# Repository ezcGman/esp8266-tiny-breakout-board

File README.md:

# ESP8266 Tiny Breakout Board
A very small (29,9x26,9mm) ESP8266 breakout board with 5V support, proper screw terminal for power wires and required resistors and caps for the ADC input!

## Credits
As for all my PCBs: Huge thanks to Quindor from QuinLED.info and also the folks from #pcb-design-talk on his Discord server! Would not have been able to do anything without these people!!

## KiCad dependencies
It might happen that KiCad is missing my custom footprints. You can find and download them here and then add them to KiCad: https://github.com/ezcGman/andys-footprints

## Key features
- It's small! A little smaller even than these cheap / billo breakout boards you bought so far on AliExpress or eBay!
- It's a real PCB and not that paper thing I just ranted about in the line above!
- 5-18V support! However, I recommend powering it with 12V max; the heat that LDO will produce might be a bit much.
- The ESP sits on pin headers instead of being soldered onto it. This enables you to remove / exchange it, e.g. if your code on that ESP doesn't have any OTA update feature, or if you want to exchange it for another ESP type
- Already comes with the necessary resistors and a stabilizing capacitor to directly use the ADC / analog input 
- A proper screw terminal for the power source / cables! No flimsy Duponts for this
- Cutout for the ESP antenna for better Wi-Fi signal
- Mounting hole to screw it onto something
- Made in Germany! ;)

## Parts list
Please see the [iBOM](/ibom/ESPBreakoutBoard-Min-Cutout-v4r3.html), which you can find in the `ibom` folder: It lists all components to easily find them on AliExpress, LCSC or your preferred component sourcing platform :)

## Tools list
### Required
- A soldering iron
- Soldering tin

### Optional
- For SMD components:
  - A hot air soldering/reflow station. However, it's only two and u have space around them, so they can be done with a soldering iron. Also the LDO can be technically soldered with an iron.
  - Solder paste
  - Tweezers

## About that 0Ω resistor - Timed Deep Sleep
If you want to use the timed deep sleep feature of the ESP8266, place a 0Ω resistor on R5, or simply bridge the pads. This will connect RST with IO16, which is required to use timed deep sleep. You can find a lot about timed deep sleep out there on how it works.

## Why the AMS117? Why not another LDO?
Because: I have so many lying around here ¯\\_(ツ)\_/¯ It's not the best, but pretty famous, cheap and easy to get LDO. It theoretically can eat up to 18V, so you could power that board with 18V, if you wanted to. Not talking about the heat this thing generates, if you would ;)

Its downsides are clearly the quiescent current of at least 5mA up to 13mA! There are also smaller LDOs (the AMS1117 is SOT-223), but with that screw terminal I wanted, it wouldn't matter anyways.
If you want to change it, you're welcome to edit the PCB using KiCad :)

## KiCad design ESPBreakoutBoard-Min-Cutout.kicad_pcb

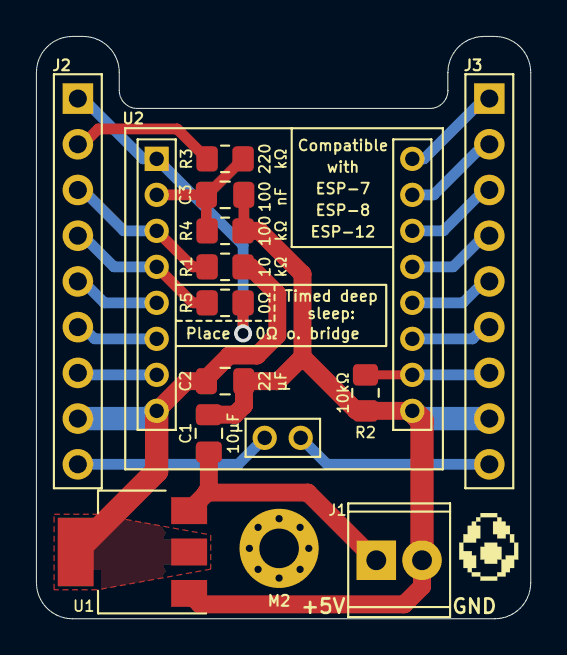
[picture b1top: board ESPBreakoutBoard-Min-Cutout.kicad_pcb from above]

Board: 2 copper layers, 27.5 x 32.3 mm, 15 parts (0 on the bottom side), 20 nets.

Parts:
C1: 10µF; C_0805_2012Metric_Pad1.18x1.45mm_HandSolder
C2: 22; C_0805_2012Metric_Pad1.18x1.45mm_HandSolder
C3: 100; C_0805_2012Metric_Pad1.18x1.45mm_HandSolder
G1: LOGO; Yoshi-Egg-Small
H1: M2; MountingHole_2.2mm_M2_Pad_Via
J1: Screw_Terminal_01x02; TerminalBlock_Phoenix_MPT-0,5-2-2.54_1x02_P2.54mm_Horizonta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
J2, J3: Conn_01x09_Male; PinHeader_1x09_P2.54mm_Vertical-Fixed-SilkScreen
R1: 10; R_0805_2012Metric_Pad1.20x1.40mm_HandSolder
R2: 10kΩ; R_0805_2012Metric_Pad1.20x1.40mm_HandSolder
R3: 220; R_0805_2012Metric_Pad1.20x1.40mm_HandSolder
R4: 100; R_0805_2012Metric_Pad1.20x1.40mm_HandSolder
R5: 0Ω; R_0805_2012Metric_Pad1.20x1.40mm_HandSolder
U1: AMS1117-3.3; SOT-223-3_TabPin2
U2: ESP-07; ESP-12-Socket-Cutout-IO9-10

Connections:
/+3.3V: C2.1, J2.8, R1.1, U1.2 (VO), U2.8 (VCC)
/+5V: C1.1, J1.1, U1.3 (VI)
/ADC: C3.1, R3.2, R4.1, U2.2 (ADC)
/ADCRAW: J2.2, R3.1
/EN: J2.3, R1.2, U2.3 (EN)
/IO15: J3.7, R2.1, U2.16 (GPIO15)
/IO16: J2.4, R5.2, U2.4 (GPIO16)
/RST: J2.1, R5.1, U2.1 (~RST)
GND: C1.2, C2.2, C3.2, J1.2, J3.8, R2.2, R4.2, U1.1 (GND), U2.15 (GND)
unnamed: J2.5, U2.5 (GPIO14)
unnamed: J2.6, U2.6 (GPIO12)
unnamed: J2.7, U2.7 (GPIO13)
unnamed: J2.9, U2.11 (GPIO9)
unnamed: J3.1, U2.22 (GPIO1/TXD)
unnamed: J3.2, U2.21 (GPIO3/RXD)
unnamed: J3.3, U2.20 (GPIO5)
unnamed: J3.4, U2.19 (GPIO4)
unnamed: J3.5, U2.18 (GPIO0)
unnamed: J3.6, U2.17 (GPIO2)
unnamed: J3.9, U2.12 (GPIO10)

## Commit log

2021-06-28 v3r3
2021-08-05 v3r4: Made some font improvements after 1st print and realizing a few labels were too small
2021-08-05 v3r4: Updated pictures
2021-12-25 Update README.md
    Fixed typo in Readme
2022-02-11 v4r1: Added IO 9&10, made board a factor of 2.54mm; KiCad 6 update
2022-02-11 v4r2: Fixed Silkscreen and 3D Models
2022-09-29 v4r3: Added gerbers, fixed odd edge cuts
2022-09-29 Added iBOM
